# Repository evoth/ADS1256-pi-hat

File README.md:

# ADS1256 Pi Hat

A simple PCB to interface up to four load cells with a Raspberry Pi using [this HiLetgo ADS1256 board](https://www.amazon.com/HiLetgo-ADS1256-Acquisition-Precision-Collecting/dp/B09KGXC44Q) and four [JST S4B-XH-A connectors](https://www.digikey.com/en/products/detail/jst-sales-america-inc/S4B-XH-A/1651041). Includes solder bridges to select separate data lines (DRDY, CS, PDWN) when connecting two boards at the same time.

This board will be used to facilitate high-speed data acquisition for rocket motor test fires, interfacing with multiple load cells and possibly a pressure transducer (PT). Data acquisition is a key responsibility of the Knights Experimental Rocketry (KXR) Launch Test Infrastructure (LTI) team, which provides test stands and data for multiple teams within KXR.

Since this is only the third PCB I've ever designed (I'm a CS major with only self-taught electronics knowledge), there are certainly improvements to be made. Ground plane, separate analog ground, sources of noise, and filtering for analog lines would be good areas of learning for a future version of this board.

## Files

The KiCad project (including schematic, board, and fabrication files) can be found in the `KXR_pi_hat_v0.2` directory.

(Ignore `KXR_pi_hat_v0.1`, which was an... interesting idea to cram 5 independent HX711 modules onto 2 boards with a single design.)

## Parts

### [HiLetgo ADS1256 Board](https://www.amazon.com/HiLetgo-ADS1256-Acquisition-Precision-Collecting/dp/B09KGXC44Q)

This HiLetgo module contains support components for the [ADS1256 ADC](https://www.ti.com/lit/ds/symlink/ads1255.pdf?ts=1750027613648) and breaks out the analog inputs and data lines. Since we only need one or two of these for our application, it made more sense to use a ready-made module than try to integrate the raw ADC chip.

**Pins**

- **5V, GND**: Power for the board. There are also separate analog grounds which were tied to the same GND for this design.
- **SCLK, DIN, DOUT**: SPI bus for communication between the Pi and ADS1256 to change settings and read data. Can be shared between multiple modules.
- **CS, DRDY, PDWN**: Additional lines for signalling during data transmission. Need to be connected to separate pins for each module.
- **AIN0-AIN7**: Analog inputs for voltage measurement. These pins can either act as 8 single-ended inputs or 4 differential inputs. Load cells give a differential signal.

### JST S4B-XH-A Connectors

These are standard 2.5mm right-angle connectors, which were selected because 2.5mm JST connectors had been used to connect load cells in previous designs.

Below is the wiring convention used in this design:

- **Pin 1**: GND/Excitation- (black)
- **Pin 2**: Signal- (white)
- **Pin 3**: Signal+ (green)
- **Pin 4**: 5V/Excitation+ (red)

### [Stacking Headers](https://www.amazon.com/Female-Stacking-Header-Compatible-Raspberry/dp/B084Q4W1PW)

We used stacking headers to allow another board to be stacked on top, but any 2x20 2.54mm pitch female headers should work for attaching the PCB to the Pi.

## Assembly

### 1. Solder headers

The headers for connecting to the Pi should be soldered first, because otherwise the ADS1256 board might get in the way. Make sure the female side is facing down (towards side with KXR logo).

### 2. Solder ADS1256 module

Solder the ADS1256 module onto the top of the board, lined up with the footprint. **It will not work if soldered on the other side!**

### 3. Solder JST connectors

Same deal, solder the connectors as marked on the PCB.

### 4. Bridge solder jumpers

Select pins for DRDY, CS, and PDWN by bridging either the left or right solder jumpers on the back of the board. See the [Jumpers](#jumpers) section for more details.

## Schematic

This should be pretty self-explanatory. J1 is connected to AIN0/1, J2 is connected to AIN2/3, etc., and the SPI lines are connected to the hardware SPI on the Pi. The solder jumpers are the only thing to watch out for.

## Jumpers

To use two boards at the same time, they will need to have separate data lines. To do this, bridge the solder jumpers on the right side for "Board 1", and the left side for "Board 2".

### "Board 1" pins:

| Pin      | GPIO   | Physical Pin # |
| -------- | ------ | -------------- |
| **DRDY** | GPIO22 | 15             |
| **CS**   | GPIO8  | 24             |
| **PDWN** | GPIO24 | 18             |

### "Board 2" pins:

| Pin      | GPIO   | Physical Pin # |
| -------- | ------ | -------------- |
| **DRDY** | GPIO23 | 16             |
| **CS**   | GPIO7  | 26             |
| **PDWN** | GPIO25 | 22             |

## Software

To use the ADS1256, find an applicable library, modifying it as needed. For example, you could clone [this repo for Waveshare boards](https://github.com/waveshareteam/High-Precision-AD-DA-Board/tree/master/RaspberryPI/ADS1256/python3) and modify `config.py` with the applicable pin numbers.

One issue you may run into is the fact that the board uses the hardware CS pin, which is often claimed by the SPI system, so it can't be used as a GPIO output. Since most ADS1256 libraries will manually set the CS pin, you will need to free up the pin to be used as an output. This can be done by changing the SPI device tree overlay to one which doesn't use the CS pin, such as `spi0-0cs`. To do this, add the line `dtoverlay=spi0-0cs` to `/boot/config.txt`, removing any conflicting dtoverlays if necessary.

Good luck!

## Pictures

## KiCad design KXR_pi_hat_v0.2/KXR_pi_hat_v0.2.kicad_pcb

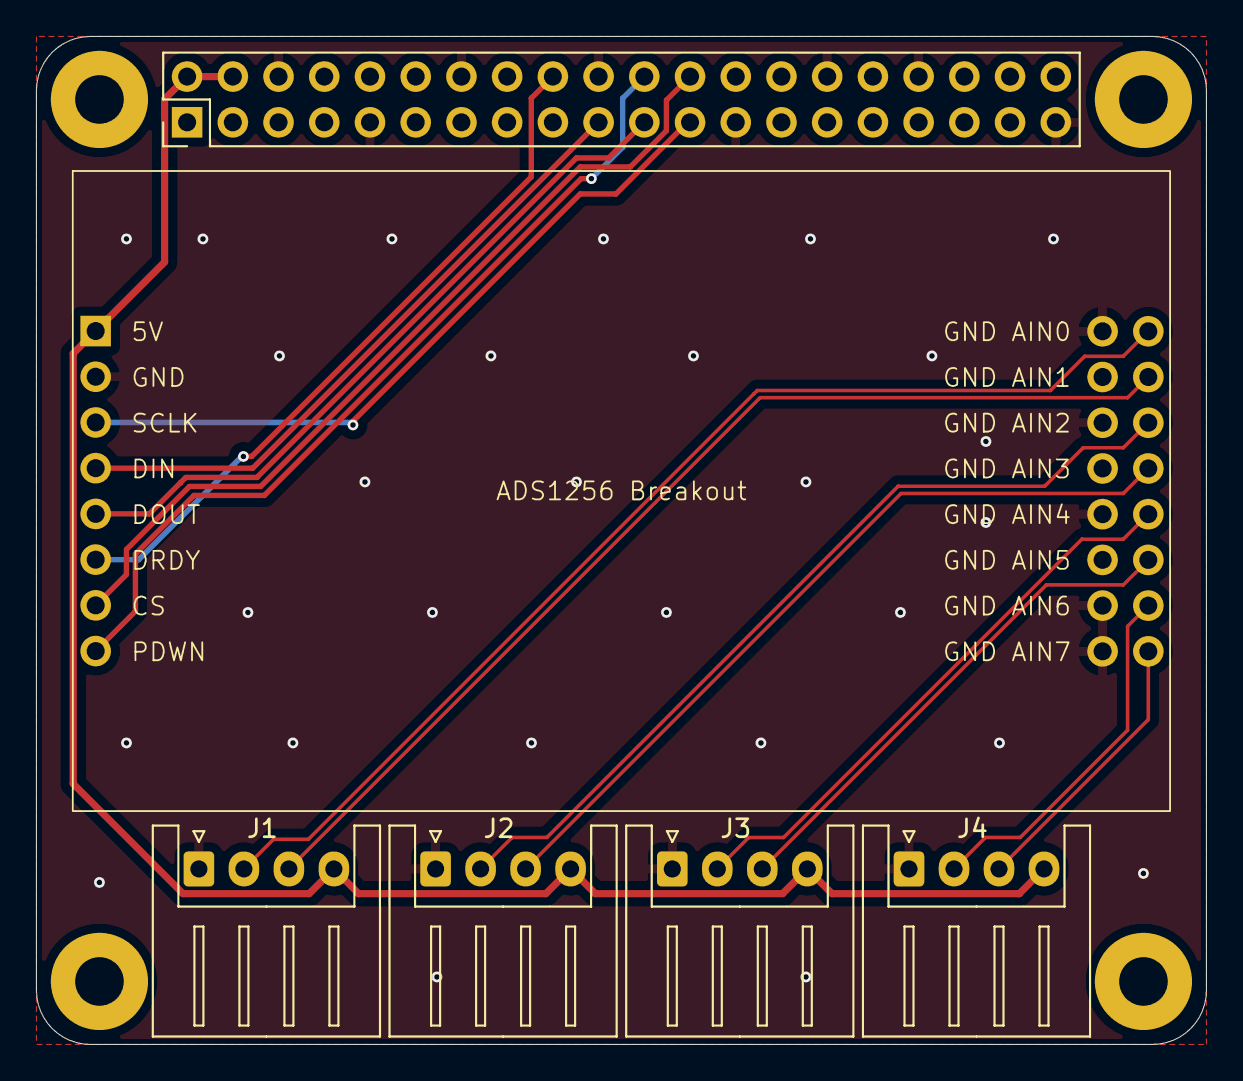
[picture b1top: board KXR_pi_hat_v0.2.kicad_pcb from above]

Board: 2 copper layers, 65.0 x 56.0 mm, 6 parts (0 on the bottom side), 16 nets.

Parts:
ADS1256 Breakout: HiLetGo_ADS1256
J1, J2, J3, J4: Conn_01x05_Pin; JST_XH_S4B-XH-A_1x04_P2.50mm_Horizontal
U2: Raspberry_Pi_2_3; PinSocket_2x20_P2.54mm_Vertical

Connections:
+5V: ADS1256 Breakout.1 (5V), J1.4, J2.4, J3.4, J4.4, U2.2 (5V), U2.4 (5V)
/CS_1: ADS1256 Breakout.7 (CS), U2.24 (~CE0/GPIO8)
/DRDY_1: ADS1256 Breakout.6 (DRDY), U2.18 (GPIO24)
/LC1_S+: ADS1256 Breakout.12 (AIN1), J1.3
/LC1_S-: ADS1256 Breakout.10 (AIN0), J1.2
/LC2_S+: ADS1256 Breakout.16 (AIN3), J2.3
/LC2_S-: ADS1256 Breakout.14 (AIN2), J2.2
/LC3_S+: ADS1256 Breakout.20 (AIN5), J3.3
/LC3_S-: ADS1256 Breakout.18 (AIN4), J3.2
/LC4_S+: ADS1256 Breakout.24 (AIN7), J4.3
/LC4_S-: ADS1256 Breakout.22 (AIN6), J4.2
/MISO: ADS1256 Breakout.5 (DOUT), U2.21 (MISO0/GPIO9)
/MOSI: ADS1256 Breakout.4 (DIN), U2.19 (MOSI0/GPIO10)
/PDWN_1: ADS1256 Breakout.8 (PDWN), U2.22 (GPIO25)
/SCLK: ADS1256 Breakout.3 (SCLK), U2.23 (SCLK0/GPIO11)
GND: ADS1256 Breakout.2 (GND), ADS1256 Breakout.9 (GND), ADS1256 Breakout.11 (GND), ADS1256 Breakout.13 (GND), ADS1256 Breakout.15 (GND), ADS1256 Breakout.17 (GND), ADS1256 Breakout.19 (GND), ADS1256 Breakout.21 (GND), ADS1256 Breakout.23 (GND), J1.1, J2.1, J3.1, J4.1, U2.6 (GND), U2.9 (GND), U2.14 (GND), U2.20 (GND), U2.25 (GND), U2.30 (GND), U2.34 (GND), U2.39 (GND)

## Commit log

2025-03-30 Notional versions v0.1 and v0.2
2025-06-15 Finishing touches and production files
2025-06-16 Added README, clarified schematic
2025-06-16 Widened JST image in README
2025-06-16 Added some pretty pictures
2025-06-16 Added info about dtoverlay I just remembered
2025-06-16 Wording changes to README
